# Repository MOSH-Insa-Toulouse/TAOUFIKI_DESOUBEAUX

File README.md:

# CAPTEUR DE GRAPHITE TAOUFIKI_DESOUBEAUX
# Sommaire
<!-- TOC depthFrom:2 -->
  - [1. Description](#1-Description)
  - [2. Code Arduino](#2-Code-Arduino)
  - [3. KiCAD](#3-KiCAD)
  - [4. Application Android](#4-Application-Android)
  - [5. Banc de tests](#5-Banc-de-tests)
  - [6. Résultats et discussion](#6-Résultats-et-discussion)
  - [7. Datasheet du capteur](#7-Datasheet-du-capteur)
  - [8. Contact](#8-Contact)
<!-- /TOC -->

# 1. Description 

Ce projet a été réalisé au cours de l'unité de formation "Du Capteur au Banc de Test" de la 4ème année du cursus “Génie Physique” à l’INSA de Toulouse.  L'objectif de ce dernier est la réalisation d'un capteur de déformation à base de graphite, peu onéreux, flexible, léger et écoresponsable.

Ce capteur exploite la dépendance entre la conductivité électrique et la distance entre les nanoparticules de graphite. En  effet, les électrons se déplacent entre les nanoparticules de graphite par effet tunnel. En appliquant de plus une contrainte mécanique, l'échantillon se déforme, ce qui affecte la distance entre les nanoparticules du capteur et modifie ainsi la conductivité électrique, ce qui se traduit par une variation de résistance, qu'on peut alors mesurer.

Pour ce faire, nous allons colorier au crayon la surface du capteur pour laisser une fine couche de graphite sur le papier. Nous avons à notre disposition plusieurs types de crayons et qui se distinguent par la concentration de graphite contenue dans chacun d'entre eux. Nous pourrons ainsi observer différents comportements de résistances en fonction des crayons utilisés.

La chaîne de mesure est basée sur l'acquisition d'un signal associée à la variation de résistance du capteur. Nous avons alors réalisé un shield PCB à l'aide du logiciel KiCad contenant un amplificateur transimpédance, un encodeur rotatoire, un module Bluetooth et un écran OLED. Ce shield est ensuite placé sur une carte Arduino UNO, programmé par un code C++ Arduino à l'aide du logiciel Arduino IDE. Les mesures de résistances sont également trannsmises par Bluetooth et interfacées sur une application Android APK créée sur MIT App Inventor.

# 2. Code Arduino

Pour développer notre code Arduino, nous avons d'abord du installer trois librairies Adafruit : Adafruit_GFX_Library et Adafruit_SSD1306 pour le contrôle de nos modules et Adafruit_BusIO pour la connexion entre SPI et I2C. 

Nous avons ensuite réalisé un code développé sous Arduino IDE, qui nous permet de contrôler un module Bluetooth, un amplificateur transimpédance et un écran OLED et permet la mesure de résistance de notre graphite. Ce code se trouve [ici](/Capteur_de_graphite.ino).

# 3. KiCad

## Empreintes et symboles

- Amplificateur LTC1050

- Module Bluetooth

- Encodeur rotatoire

- Ecran OLED

## Schématique et circuit

## Visualisation 3D

# 4. Application Android

Nous avons réalisé une application Android, via le site Internet MIT App Inventor. Celle-ci assure la liaison Bluetooth avec notre Shield et permet d'afficher l'évolution relative de la résistance en temps réel dans un graph.

## Code

## Interface

# 5. Banc de tests

Notre banc de test est composé d'une carte Arduino sur laquelle on a placé notre shield et branchée par un câble USB à l'ordinateur. Les pinces crocodiles permettent d'immobiliser le capteur de graphite et de relever les mesures de résistance.

Afin de mesurer les variations de résistance, nous avons utilisé un dispositif composé de demi-cercles concentriques, dont le rayon varie de 1 à 2,5 cm.

On place d'abord les pinces crocodiles sur le capteur, après avoir colorié ce dernier avec le crayon qui nous intéresse pour la mesure. On place ensuite notre capteur sur le demi-cercle au rayon le plus grand, pour éviter de trop abimer le capteur dès le début. On repète cette dernière opération jusqu'à arriver au demi-cercle de plus petit rayon.

# 6. Résultats et discussion

## Résultats
Avec ce banc de tests, nous obtenons les courbes suivantes réalisées sous Python, représentant l'évolution de la variation relative de résistance en fonction de la déformation et leurs courbes de tendance; ainsi qu'un graph comparant les résultats pour les 3 types de crayons testés:

Plusieurs remarques peuvent être faites :
- Les courbes suivent une évolution quasi-linéaire.
- Parmi les trois types de crayons testés, ce sont les variations de résistance des crayons H et B qui semblent les plus constantes en fonction de la déformation. On aurait pu s'attendre à ce que plus le crayon soit dur, plus la variation de résistance soit élevée. Ce n'est pas notre cas ici. Il aurait fallu tester avec plus de crayons différents pour voir une tendance plus marquée ou faire plus d'essais. Vous pouvez retrouver le détail des mesures rassemblées dans un fichier Excel [ici](/Mesures).
- Nous obtenons comme facteurs de jauge : 1,37 pour le crayon H, 1,89 pour le crayon B et 52,7 pour le crayon HB.

## Discussion

Deux limites principales sont ici à mentionner quant à l'utilisation de ce banc de tests :
- La non-répétabilité des mesures : en effet, lors du relevé des mesures, le plus infime des mouvements pouvait faire varier la résistance du tout au tout, il était donc difficile d'obtenir des valeurs de résistance proches l'une de l'autre d'un essai à l'autre.
- Le dépôt de graphite : déposer trop peu de graphite pouvait entraîner des problèmes de continuité électrique; il faut aussi prendre en compte la précision du tracé ou encore la pression du crayon sur le papier qui peut varier d'un essai à l'autre et entraîner des variations du facteur de jauge.

# 7. Datasheet du capteur

Vous pouvez retrouver notre datasheet [ici](/Datasheet).

# 8. Contact

Nous tenons à remercier tous nos professeurs pour leur aide lors de l'élaboration de ce projet, notamment M. Grisolia, Mme. Crouzet et M. Biganzoli.

Pour toute question, merci de nous contacter : 
- Ines TAOUFIKI : taoufiki@etud.insa-toulouse.fr
- Juliette DESOUBEAUX : desoubea@etud.insa-toulouse.fr

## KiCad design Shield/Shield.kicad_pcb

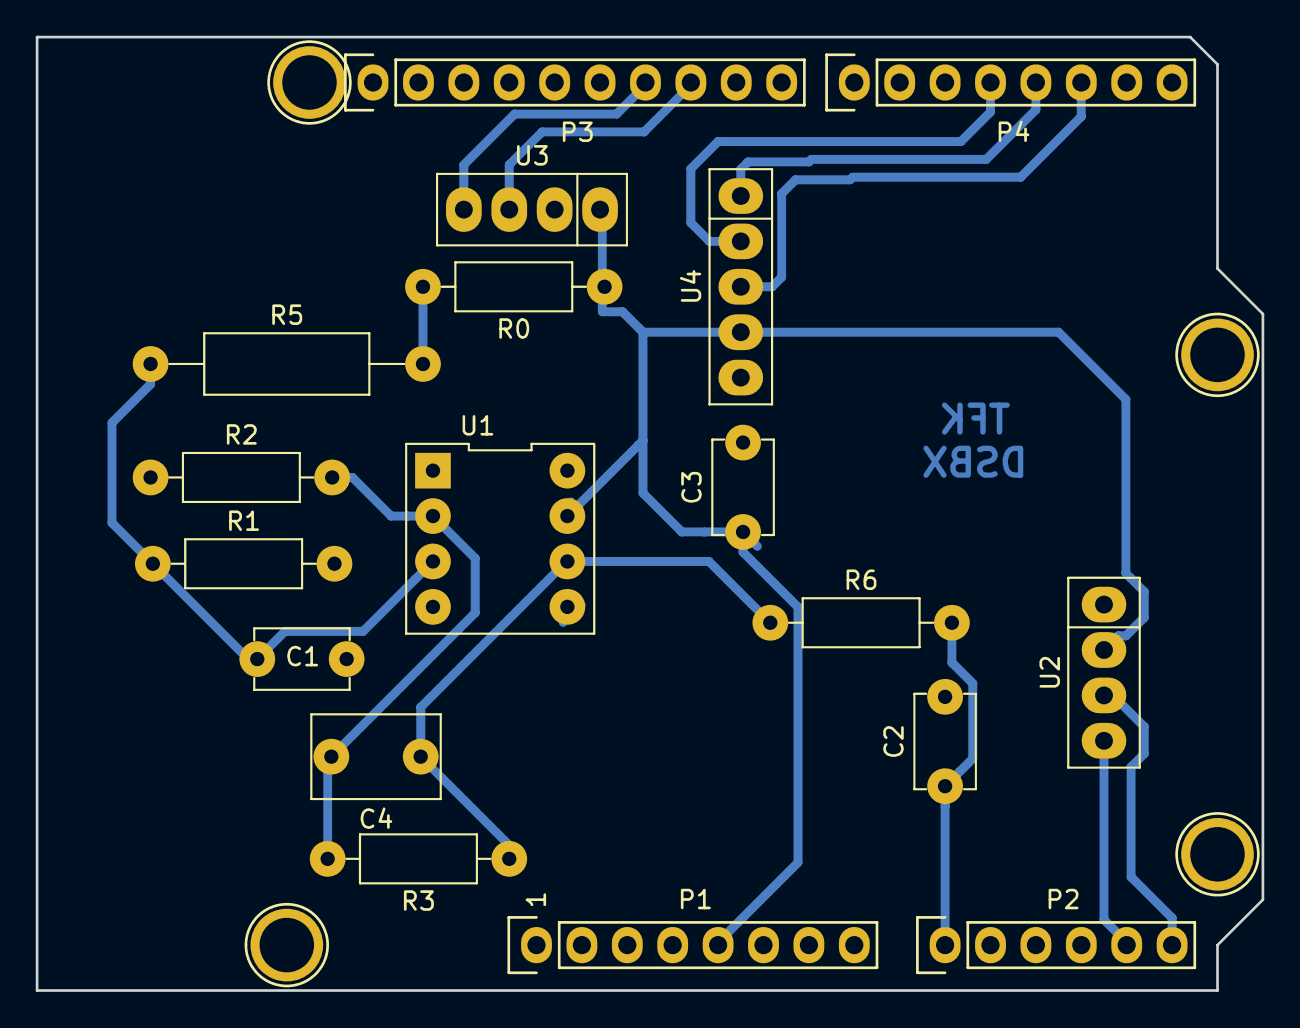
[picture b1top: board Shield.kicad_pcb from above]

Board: 2 copper layers, 68.6 x 53.3 mm, 22 parts (0 on the bottom side), 14 nets.

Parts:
C1, C2, C3: 100n; C_Disc_D5.1mm_W3.2mm_P5.00mm
C4: 1u; C_Rect_L7.0mm_W4.5mm_P5.00mm
P1: Power; Socket_Strip_Arduino_1x08
P2: Analog; Socket_Strip_Arduino_1x06
P3: Digital; Socket_Strip_Arduino_1x10
P4: Digital; Socket_Strip_Arduino_1x08
P5, P6, P7, P8: CONN_01X01; Arduino_1pin
R0: Rsensor; R_Axial_DIN0207_L6.3mm_D2.5mm_P10.16mm_Horizontal
R1, R3: 100k; R_Axial_DIN0207_L6.3mm_D2.5mm_P10.16mm_Horizontal
R2, R6: 1k; R_Axial_DIN0207_L6.3mm_D2.5mm_P10.16mm_Horizontal
R5: 10k; R_Axial_DIN0309_L9.0mm_D3.2mm_P15.24mm_Horizontal
U1: LTC1050; AOP
U2: OLED_0,91; Mon_Bluetooth
U3: Bluetooth_HC05; Mon_Bluetooth
U4: KY_040; Encodeur

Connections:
+5V: C3.1, P1.5, R0.1, U1.7, U2.2, U3.1, U4.4
ADC: C2.1, P2.1, R6.2
CLK: P4.5, U4.1
DATA: P4.4, U4.2
GND: C1.2, C2.2, C3.2, P1.6, P1.7, P3.4, R1.2, R2.1, U1.4, U2.1, U3.2, U4.5
IN+: C1.1, R1.1, R5.1, U1.3
IN-: C4.2, R2.2, R3.2, U1.2
unnamed: C4.1, R3.1, R6.1, U1.6
unnamed: R0.2, R5.2
RX: P3.8, U3.3
SCK: P2.6, P3.1, U2.3
SDA: P2.5, P3.2, U2.4
SWITCH: P4.6, U4.3
TX: P3.7, U3.4
